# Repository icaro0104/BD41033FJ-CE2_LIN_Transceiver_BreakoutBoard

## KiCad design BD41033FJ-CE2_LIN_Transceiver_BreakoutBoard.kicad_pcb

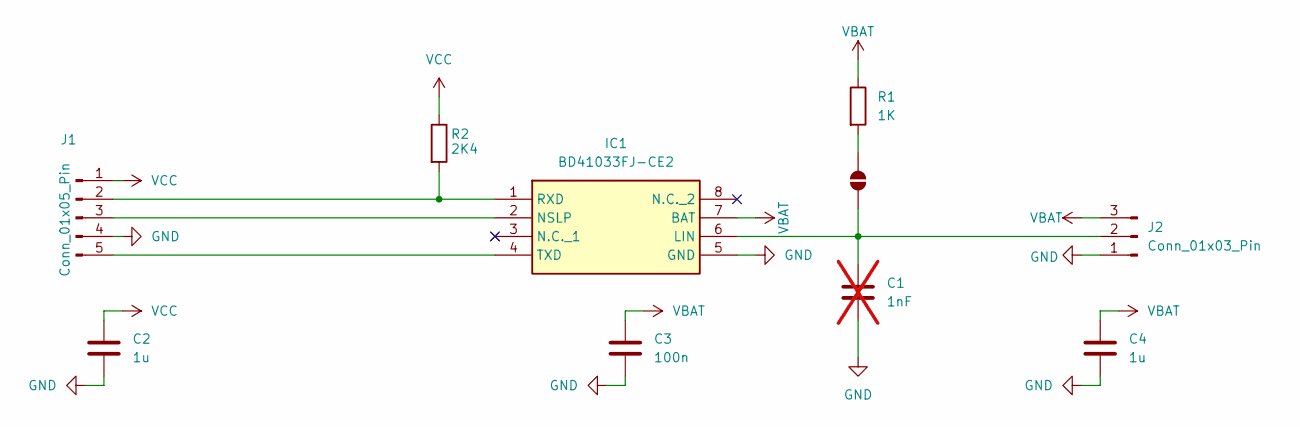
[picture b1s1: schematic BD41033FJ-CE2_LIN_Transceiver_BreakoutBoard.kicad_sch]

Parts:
C1: 1nF; C_0805_2012Metric_Pad1.18x1.45mm_HandSolder; not fitted
C2, C4: 1u; C_0805_2012Metric_Pad1.18x1.45mm_HandSolder
C3: 100n; C_0805_2012Metric_Pad1.18x1.45mm_HandSolder
IC1: BD41033FJ-CE2; SOP-8_3.9x4.9mm_P1.27mm; Mouser Part Number 755-BD41033FJ-CE2
J1: Conn_01x05_Pin; PinHeader_1x05_P2.54mm_Vertical
J2: Conn_01x03_Pin; PinHeader_1x03_P2.54mm_Vertical
JP1: SolderJumper_2_Open; SolderJumper-2_P1.3mm_Open_TrianglePad1.0x1.5mm
R1: 1K; R_0805_2012Metric_Pad1.20x1.40mm_HandSolder
R2: 2K4; R_0805_2012Metric_Pad1.20x1.40mm_HandSolder

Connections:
GND: C1.2, C2.2, C3.2, C4.2, IC1.5 (GND), J1.4, J2.1
unnamed: C1.1, IC1.6 (LIN), J2.2, JP1.1 (A)
unnamed: IC1.2 (NSLP), J1.3
unnamed: IC1.1 (RXD), J1.2, R2.2
unnamed: IC1.4 (TXD), J1.5
unnamed: JP1.2 (B), R1.2
VBAT: C3.1, C4.1, IC1.7 (BAT), J2.3, R1.1
VCC: C2.1, J1.1, R2.1

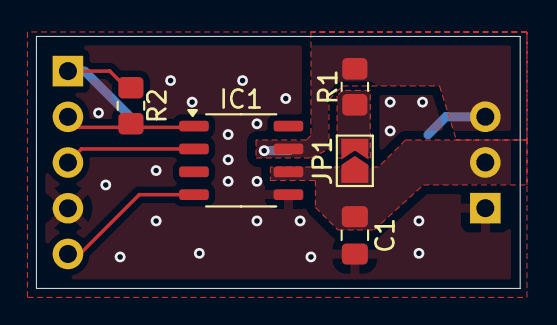
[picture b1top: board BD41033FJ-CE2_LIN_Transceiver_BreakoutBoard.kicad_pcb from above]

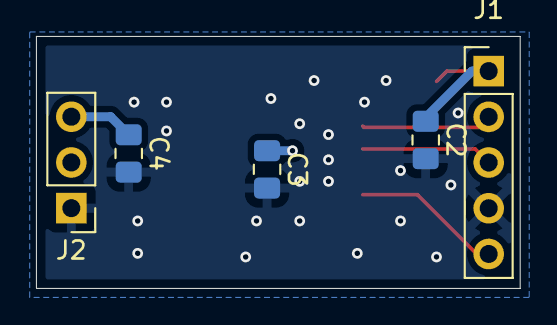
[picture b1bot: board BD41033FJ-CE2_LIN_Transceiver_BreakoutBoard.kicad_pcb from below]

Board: 2 copper layers, 26.9 x 14.0 mm, 10 parts (5 on the bottom side), 8 nets.
